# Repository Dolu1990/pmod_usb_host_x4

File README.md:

Important !

- The PMOD connector is on the bottom side of the PCB in kicad, but should be solder on the top.
- The 5V pin of the board need to be connected to your main board 5V. (the design was made during covid, when all the buckboost went out of stock XD)

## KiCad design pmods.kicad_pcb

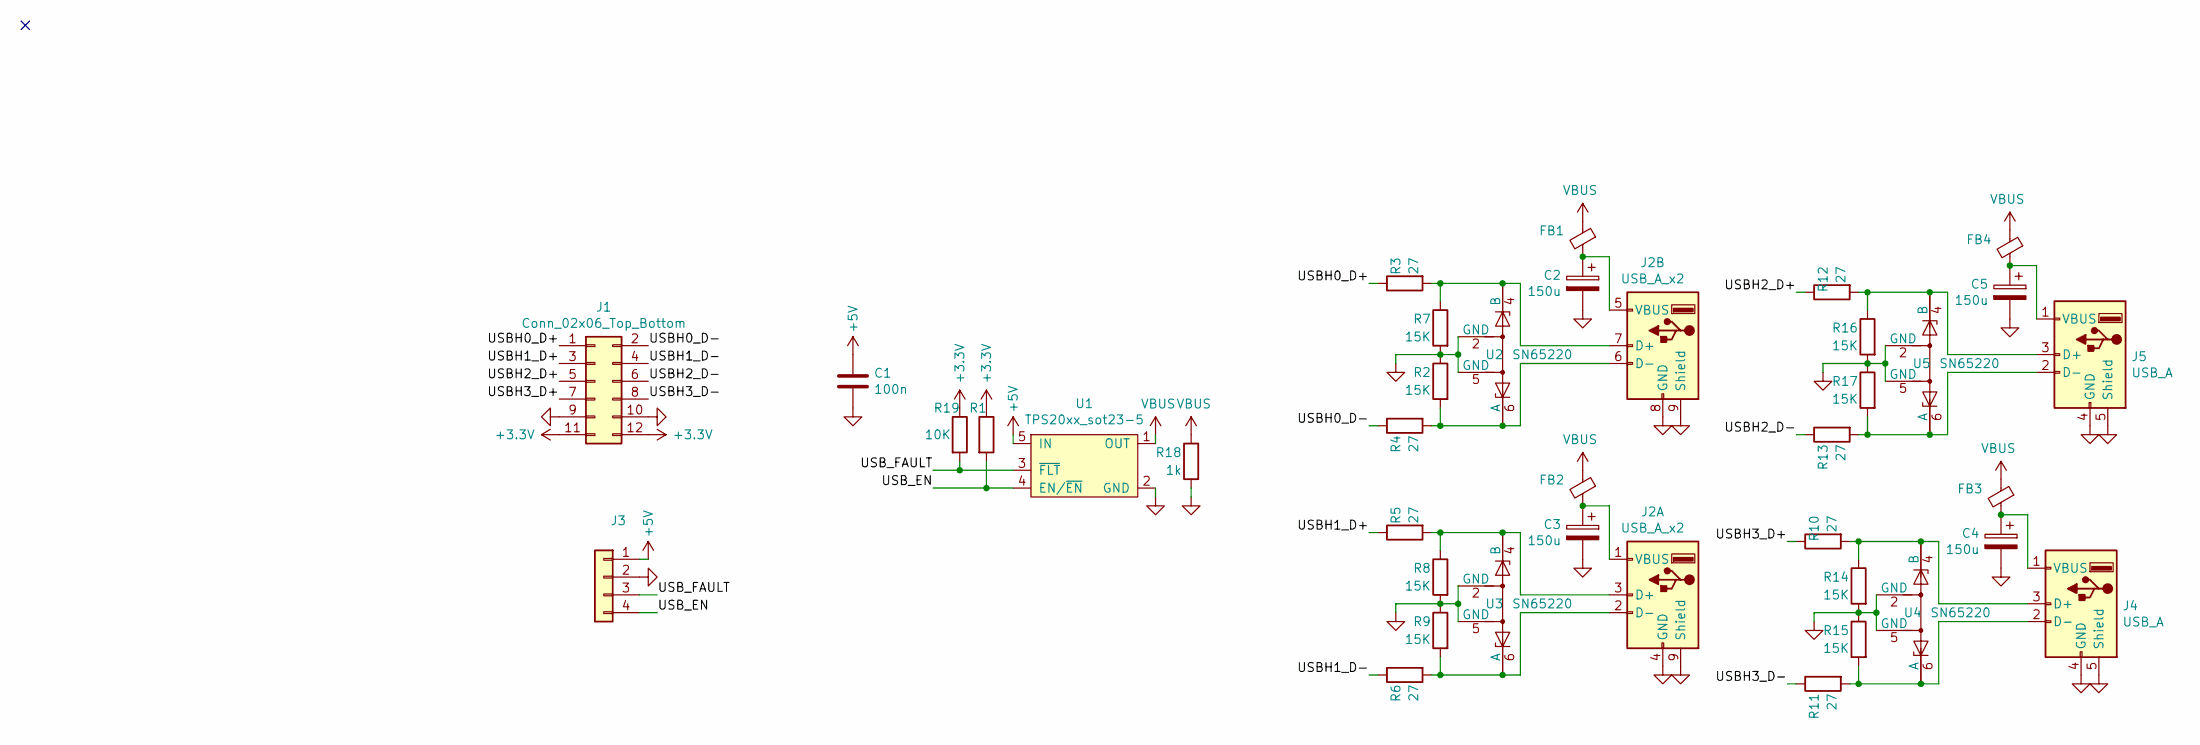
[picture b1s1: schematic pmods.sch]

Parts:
C1: 100n; C_0603_1608Metric_Pad1.08x0.95mm_HandSolder
C2, C3, C4, C5: 150u; C_1206_3216Metric_Pad1.33x1.80mm_HandSolder
FB1, FB2, FB3, FB4: Ferrite_Bead_Small; L_0805_2012Metric_Pad1.05x1.20mm_HandSolder
J1: Conn_02x06_Top_Bottom; PinHeader_2x06_P2.54mm_Horizontal
J2: USB_A_x2; USB_A_Wuerth_61400826021_Horizontal_Stacked
J3: Conn_01x04; PinHeader_1x04_P2.54mm_Vertical
J4, J5: USB_A; USB_A_Molex_105057_Vertical
R1, R19: 10K; R_0603_1608Metric
R2, R7, R8, R9, R14, R15, R16, R17: 15K; R_0603_1608Metric
R3, R4, R5, R6, R10, R11, R12, R13: 27; R_0603_1608Metric
R18: 1k; R_0603_1608Metric
U1: TPS20xx_sot23-5; SOT-23-5
U2, U3, U4, U5: SN65220; SOT-23-6

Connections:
+3V3: J1.11, J1.12, R1.1, R19.1
+5V: C1.1, J3.1, U1.5 (IN)
/USBH0_D+: J1.1, R3.1
/USBH0_D-: J1.2, R4.1
/USBH1_D+: J1.3, R5.1
/USBH1_D-: J1.4, R6.1
/USBH2_D+: J1.5, R12.1
/USBH2_D-: J1.6, R13.1
/USBH3_D+: J1.7, R10.1
/USBH3_D-: J1.8, R11.1
/USB_EN: J3.4, R1.2, U1.4 (EN/~EN~)
/USB_FAULT: J3.3, R19.2, U1.3 (~FLT~)
GND: C1.2, C2.2, C3.2, C4.2, C5.2, J1.9, J1.10, J2.4 (GND), J2.8 (GND), J2.9 (Shield), J3.2, J4.4 (GND), J4.5 (Shield), J5.4 (GND), J5.5 (Shield), R2.1, R7.2, R8.2, R9.1, R14.2, R15.1, R16.2, R17.1, R18.2, U1.2 (GND), U2.2 (GND), U2.5 (GND), U3.2 (GND), U3.5 (GND), U4.2 (GND), U4.5 (GND), U5.2 (GND), U5.5 (GND)
unnamed: C2.1, FB1.2, J2.5 (VBUS)
unnamed: C3.1, FB2.2, J2.1 (VBUS)
unnamed: C4.1, FB3.2, J4.1 (VBUS)
unnamed: C5.1, FB4.2, J5.1 (VBUS)
unnamed: J2.2 (D-), R6.2, R9.2, U3.6 (A)
unnamed: J2.3 (D+), R5.2, R8.1, U3.4 (B)
unnamed: J2.6 (D-), R2.2, R4.2, U2.6 (A)
unnamed: J2.7 (D+), R3.2, R7.1, U2.4 (B)
unnamed: J4.2 (D-), R11.2, R15.2, U4.6 (A)
unnamed: J4.3 (D+), R10.2, R14.1, U4.4 (B)
unnamed: J5.2 (D-), R13.2, R17.2, U5.6 (A)
unnamed: J5.3 (D+), R12.2, R16.1, U5.4 (B)
VBUS: FB1.1, FB2.1, FB3.1, FB4.1, R18.1, U1.1 (OUT)

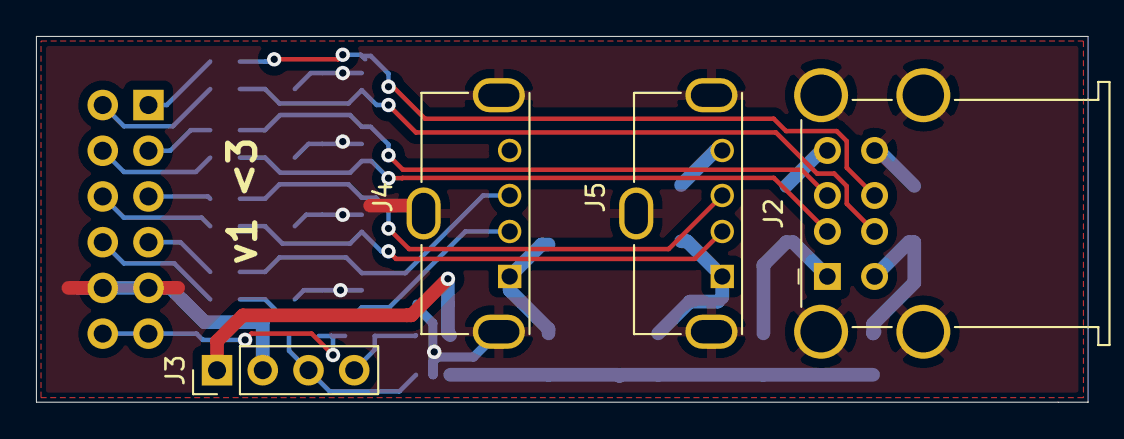
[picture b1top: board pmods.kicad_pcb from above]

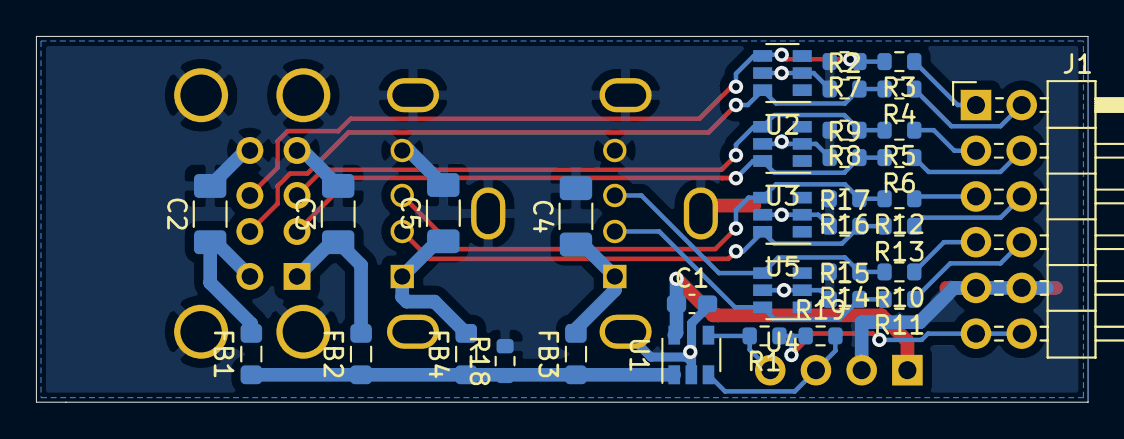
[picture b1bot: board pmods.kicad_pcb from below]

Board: 2 copper layers, 58.4 x 20.3 mm, 38 parts (34 on the bottom side), 26 nets.

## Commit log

2021-05-07 add pdf
2021-05-29 add readme
